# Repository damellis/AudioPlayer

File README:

Simple, Arduino-compatible audio player, designed to be produced using
Seeedstudio's PCBA service (http://www.seeedstudio.com/service/index.php).
Only uses parts from the Seeedstudio open parts library (OPL), including
an ATmega328, micro-SD card slot, lipo connector and charging circuit,
headphone jack, etc. The full list of parts in the OPL can be found here:
http://www.seeedstudio.com/wiki/Open_parts_library

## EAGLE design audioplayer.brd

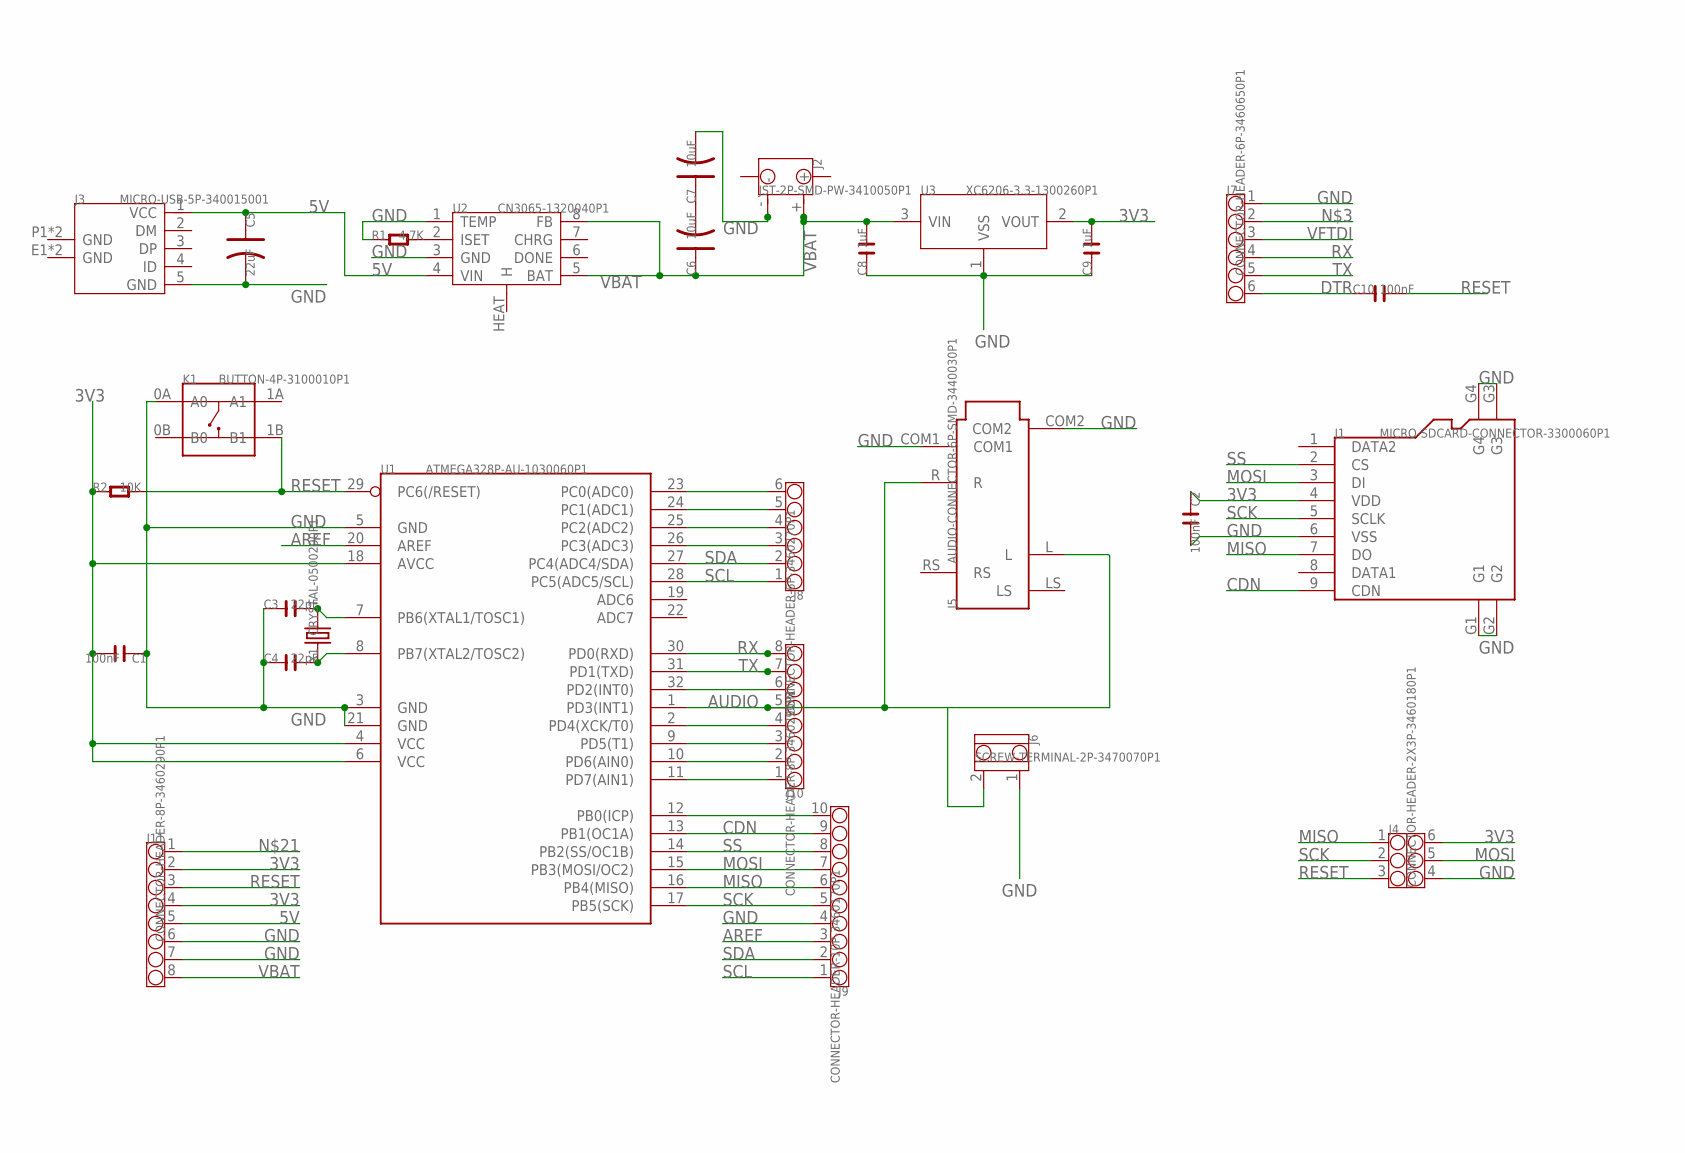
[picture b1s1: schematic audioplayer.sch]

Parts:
C1, C2, C10: 100nF; C0603
C3, C4: 22pF; C0603
C5: 22uF; AVX-B
C6, C7: 10uF; AVX-A
C8, C9: 1uF; C0805
J1: MICRO-SDCARD-CONNECTOR-3300060P1; 9P-SMD-W-RING
J2: JST-2P-SMD-PW-3410050P1; 2P-SMD-2.0-90D
J3: MICRO-USB-5P-340015001; B-SMD-5P
J4: CONNECTOR-HEADER-2X3P-3460180P1; 2X3P-2.54-2.54-11.6-3.0-BLACK-MALE
J5: AUDIO-CONNECTOR-6P-SMD-3440030P1; 6P-SMD-3.5
J6: SCREW-TERMINAL-2P-3470070P1; 2P-3.5
J7: CONNECTOR-HEADER-6P-3460650P1; 1X6P-2.54-2.54-11.6-3.0-BLACK-MALE
J8: CONNECTOR-HEADER-6P-3460270P1; 1X6P-2.54-8.5-BLACK-FEMALE
J9: CONNECTOR-HEADER-10P-3460170P1; 1X10P-2.54-8.5-YELLOW-FEMALE
J10, J11: CONNECTOR-HEADER-8P-3460290P1; 1X8P-2.54-8.5-BLACK-FEMALE
K1: BUTTON-4P-3100010P1; 4P-SMD-6.0X6.0X5.0H
R1: 4.7K; R0603
R2: 10K; R0603
U1: ATMEGA328P-AU-1030060P1; TQFP32
U2: CN3065-1320040P1; DFN8
U3: XC6206-3.3-1300260P1; SOT23
X1: CRYSTAL-0500290P1; 2P-SMD-5.0X3.2

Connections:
3V3: C1.2, C2.1, C9.2, J1.4 (VDD), J4.6, J11.2, J11.4, R2.1, U1.4 (VCC), U1.6 (VCC), U1.18 (AVCC), U3.2 (VOUT)
5V: C5.+ (1), J3.1 (VCC), J11.5, U2.4 (VIN)
AREF: J9.3, U1.20 (AREF)
AUDIO: J5.L, J5.R, J6.2, J10.5, U1.1 (PD3(INT1))
CDN: J1.9 (CDN), J9.9, U1.13 (PB1(OC1A))
DTR: C10.1, J7.6
GND: C1.1, C2.2, C3.1, C4.1, C5.- (2), C7.- (2), C8.1, C9.1, J1.6 (VSS), J1.G1, J1.G2, J1.G3, J1.G4, J2.-, J3.5 (GND), J4.4, J5.COM1, J5.COM2, J6.1, J7.1, J9.4, J11.6, J11.7, K1.0A (A0), R1.1, U1.3 (GND), U1.5 (GND), U1.21 (GND), U2.1 (TEMP), U2.3 (GND), U3.1 (VSS)
MISO: J1.7 (DO), J4.1, J9.6, U1.16 (PB4(MISO))
MOSI: J1.3 (DI), J4.5, J9.7, U1.15 (PB3(MOSI/OC2))
unnamed: C6.- (2), C7.+ (1)
unnamed: R1.2, U2.2 (ISET)
unnamed: J8.3, U1.26 (PC3(ADC3))
unnamed: J8.4, U1.25 (PC2(ADC2))
unnamed: J8.5, U1.24 (PC1(ADC1))
unnamed: J8.6, U1.23 (PC0(ADC0))
unnamed: J9.10, U1.12 (PB0(ICP))
unnamed: J10.1, U1.11 (PD7(AIN1))
unnamed: J10.2, U1.10 (PD6(AIN0))
unnamed: J10.3, U1.9 (PD5(T1))
unnamed: J10.4, U1.2 (PD4(XCK/T0))
unnamed: J10.6, U1.32 (PD2(INT0))
unnamed: C3.2, U1.7 (PB6(XTAL1/TOSC1)), X1.2
unnamed: C4.2, U1.8 (PB7(XTAL2/TOSC2)), X1.1
RESET: C10.2, J4.3, J11.3, K1.1B (B1), R2.2, U1.29 (PC6(/RESET))
RX: J7.4, J10.8, U1.30 (PD0(RXD))
SCK: J1.5 (SCLK), J4.2, J9.5, U1.17 (PB5(SCK))
SCL: J8.1, J9.1, U1.28 (PC5(ADC5/SCL))
SDA: J8.2, J9.2, U1.27 (PC4(ADC4/SDA))
SS: J1.2 (CS), J9.8, U1.14 (PB2(SS/OC1B))
TX: J7.5, J10.7, U1.31 (PD1(TXD))
VBAT: C6.+ (1), C8.2, J2.+, J11.8, U2.5 (BAT), U2.8 (FB), U3.3 (VIN)
VFTDI: J7.3

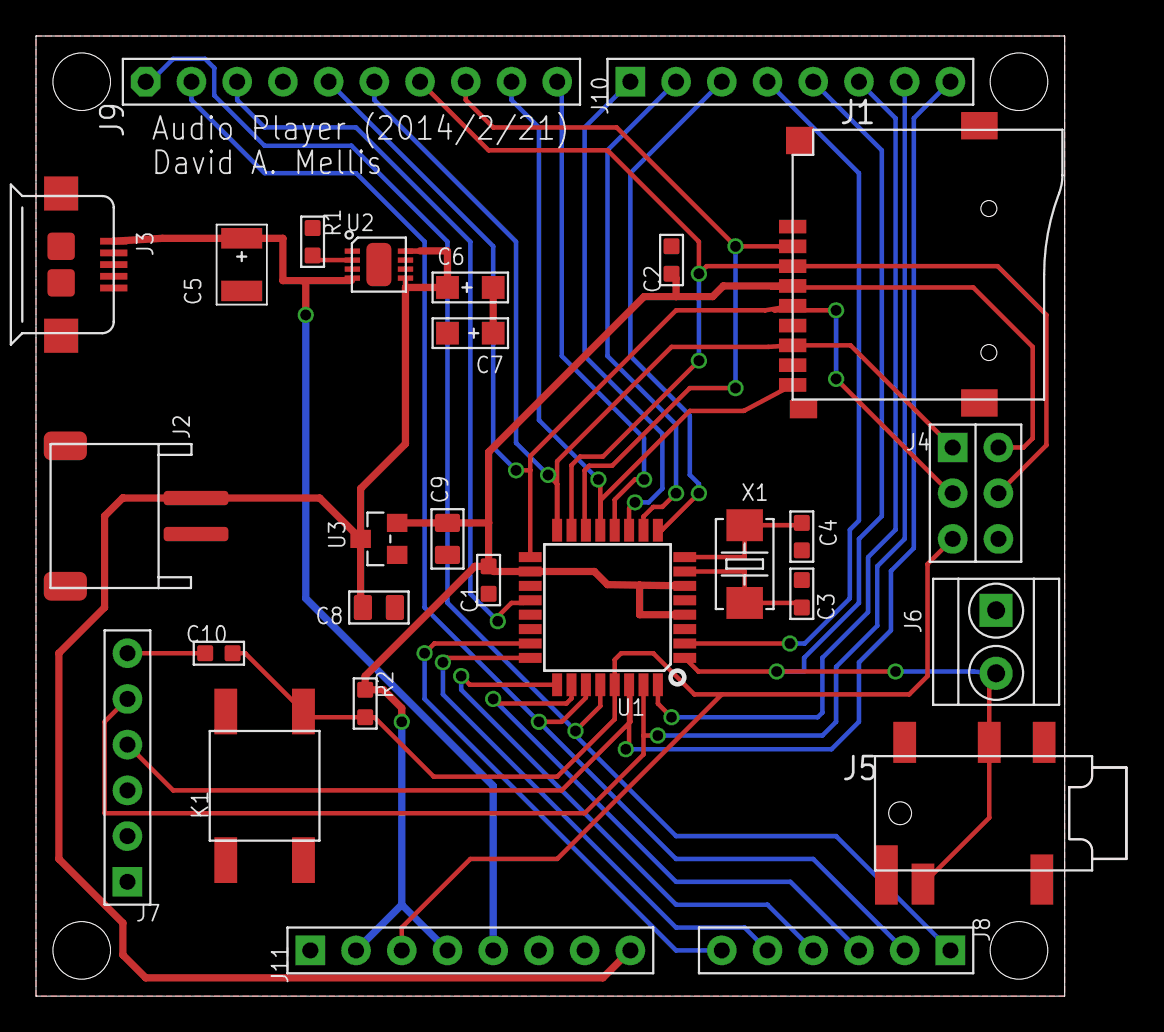
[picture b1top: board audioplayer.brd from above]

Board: 4 copper layers, 60.6 x 53.3 mm, 28 parts (0 on the bottom side), 31 nets.

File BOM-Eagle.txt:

"Part";"Value";"Device";"Package";"Description";"";
"C1";"100nF";"C-0603";"C0603";"";"";
"C2";"100nF";"C-0603";"C0603";"";"";
"C3";"22pF";"C-0603";"C0603";"";"";
"C4";"22pF";"C-0603";"C0603";"";"";
"C5";"22uF";"C-POLAR-B";"AVX-B";"";"";
"C6";"10uF";"C-POLAR-A";"AVX-A";"";"";
"C7";"10uF";"C-POLAR-A";"AVX-A";"";"";
"C8";"1uF";"C-0805";"C0805";"";"";
"C9";"1uF";"C-0805";"C0805";"";"";
"C10";"100nF";"C-0603";"C0603";"";"";
"J1";"MICRO-SDCARD-CONNECTOR-3300060P1";"MICRO-SDCARD-CONNECTOR-3300060P1";"9P-SMD-W-RING";"Micro SD Card";"";
"J2";"JST-2P-SMD-PW-3410050P1";"JST-2P-SMD-PW-3410050P1";"2P-SMD-2.0-90D";"";"";
"J3";"MICRO-USB-5P-340015001";"MICRO-USB-5P-340015001";"B-SMD-5P";"ST-USB-001E：MICRO USB B SMD R/A";"";
"J4";"CONNECTOR-HEADER-2X3P-3460180P1";"CONNECTOR-HEADER-2X3P-3460180P1";"2X3P-2.54-2.54-11.6-3.0-BLACK-MALE";"";"";
"J5";"AUDIO-CONNECTOR-6P-SMD-3440030P1";"AUDIO-CONNECTOR-6P-SMD-3440030P1";"6P-SMD-3.5";"";"";
"J6";"SCREW-TERMINAL-2P-3470070P1";"SCREW-TERMINAL-2P-3470070P1";"2P-3.5";"";"";
"J7";"CONNECTOR-HEADER-6P-3460650P1";"CONNECTOR-HEADER-6P-3460650P1";"1X6P-2.54-2.54-11.6-3.0-BLACK-MALE";"";"";
"J8";"CONNECTOR-HEADER-6P-3460270P1";"CONNECTOR-HEADER-6P-3460270P1";"1X6P-2.54-8.5-BLACK-FEMALE";"";"";
"J9";"CONNECTOR-HEADER-10P-3460170P1";"CONNECTOR-HEADER-10P-3460170P1";"1X10P-2.54-8.5-YELLOW-FEMALE";"";"";
"J10";"CONNECTOR-HEADER-8P-3460290P1";"CONNECTOR-HEADER-8P-3460290P1";"1X8P-2.54-8.5-BLACK-FEMALE";"";"";
"J11";"CONNECTOR-HEADER-8P-3460290P1";"CONNECTOR-HEADER-8P-3460290P1";"1X8P-2.54-8.5-BLACK-FEMALE";"";"";
"K1";"BUTTON-4P-3100010P1";"BUTTON-4P-3100010P1";"4P-SMD-6.0X6.0X5.0H";"";"";
"R1";"4.7K";"R-0603";"R0603";"";"";
"R2";"10K";"R-0603";"R0603";"";"";
"U1";"ATMEGA328P-AU-1030060P1";"ATMEGA328P-AU-1030060P1";"TQFP32";"8-bit AVR";"";
"U2";"CN3065-1320040P1";"CN3065-1320040P1";"DFN8";"USB-Compatible Lithiumt-Ion Battery Charger with Thermal Regulation";"";
"U3";"XC6206-3.3-1300260P1";"XC6206-3.3-1300260P1";"SOT23";"LOW ESR Cap.Compatible Positive Voltage Regulators";"";
"X1";"CRYSTAL-0500290P1";"CRYSTAL-0500290P1";"2P-SMD-5.0X3.2";"";"";

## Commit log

2014-02-06 2 hr. Basic parts and some connections.
2014-02-06 0 hr. Removing backups.
2014-02-06 1 hr: Finished basic components and schematic.
2014-02-06 0.25 hrs: initial placement of components on board.
2014-02-11 1 hr. Add Arduino-compatible headers and redo layout (and commit brd file!).
2014-02-13 1.5 hrs: routing.
2014-02-20 2 hrs. Routing the rest of the traces. Fix reset button.
2014-02-21 0.5 hrs: extend outline, add drill holes, adjust traces and components.
2014-02-21 0.25 hours: silkscreen and move FTDI header.
2014-02-24 0.5 hrs: improve trace and via spacing, move ATmega capacitor, update date.
2014-02-24 0 hr: add Seeedstudio Eagle libraries.
2014-02-24 1 hr. Generate gerbers and BOM. Order boards.
2014-02-24 0 hr: remove .DS_Store file.
2014-02-24 0 hr. Add readme.
2014-03-08 0 hrs. Move hardware files into Eagle/ directory.
2014-03-08 0 hrs. Add wavehc20110919 library (https://code.google.com/p/wavehc/).
2014-03-08 1.75 hrs. Test board and get audio playback working.
    Modifying the wavehc library to use PWM output on pin 3 (OCR2B) instead of via a DAC.
